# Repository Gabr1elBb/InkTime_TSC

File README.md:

## InkTime - Smartwatch Project
Open-source smartwatch hardware project based on the Nordic nRF52840 MCU, 
featuring a 1.54" e-paper display and optimized for ultra-low power consumption. 

## Block Diagram
```text
[ USB Type-C ]     [ LiPo Battery (250mAh) ]
           | 5V VBUS          |
           v                  | BAT
    +---------------+         v
    |    BQ25180    |<--+ [MAX17048]
    |  (Charger IC) |   | (Fuel Gauge)
    +---------------+   |     |
           | VSYS       +-----+ I2C
           v                  v
    +---------------+      +-------------+
    |    RT6160     |      |             |
    | (Buck-Boost)  |      |  nRF52840   |
    +---------------+      |     MCU     |
           | 3.3V (VDD_3V3)|  (Control   |
           | System Rail   |    Hub)     |
           |               |             |
 +---------+---------------+------+------+
 |         |               |      |
 |         v               |      |
 |  +-------------+        |      | SPI
 |  | PFET Switch |<--GPIO-+      v
 |  +------+------+        |  +-------------+
 |         | VEPD          |  | 1.54" E-paper|
 |         v               |  |   Display   |
 |  +-------------+        |  +-------------+
 |  | [Display]   |        |
 |  +-------------+        | I2C Bus
 |                         |
 +---I2C==> [ BMA421 Accel ]
 |                         |
 +---I2C==> [ DRV2605L Driver ] --> [ Vibration Motor ]
 |
 |          [ PCB Antenna ] <--> [ BLE RF ]
 |
 +---GPIO-> [ User Buttons ]
```

## Bill Of Materials (BOM)

| Designator | Component | Package | Manufacturer | Description / Notes |
| :--- | :--- | :--- | :--- | :--- |
| **U1** | [**nRF52840**](https://www.nordicsemi.com/Products/nRF52840) | aQFN-73 | Nordic Semi | SoC Bluetooth 5.0 (Procesor principal) |
| **IC1** | [**BQ25180Y**](https://www.ti.com/product/BQ25180) | DSBGA-8 | Texas Inst. | Charger IC Li-Ion (Management baterie) |
| **IC2** | [**DRV2605Y**](https://www.ti.com/product/DRV2605) | DSBGA-9 | Texas Inst. | Haptic Driver (Control motor vibrații) |
| **IC9** | [**RT6160AWSC**](https://www.richtek.com/Products/Product%20List/RT6160) | WLCSP-15 | RICHTEK | Buck-Boost Regulator 3.3V |
| **IC3** | [**BMA423**](https://www.bosch-sensortec.com/products/motion-sensors/accelerometers/bma423/) | LGA-12 | BOSCH | Accelerometru (Detectie miscare) |
| **U3 / IC6** | [**MAX17048**](https://www.analog.com/en/products/max17048.html) | TDFN-8 | Maxim/ADI | Monitorizare nivel baterie (Fuel Gauge) |
| **ANT1** | [**2450AT18B100E**](https://www.johansontechnology.com/datasheets/2450AT18B100E.pdf) | 1.4mm | JOHANSON | Antena Chip 2.45GHz |
| **J1** | [**503480-2400**](https://www.molex.com/en-us/products/part-detail/5034802400) | FPC-24 | Molex | Conector ecran (0.5mm pitch) |
| **J4** | [**KH-TYPE-C-16P**](https://www.kinghelm.com.cn/product-item-1589.html) | SMT | Kinghelm | Port USB Type-C |
| **Q3** | [**SI1308EDL**](https://www.vishay.com/en/product/71996/) | SOT-323 | Vishay | MOSFET N-Ch (Comutare putere) |
| **D3** | [**USBLC6-2**](https://www.st.com/en/protection-devices/usblc6-2sc6y.html) | SOT-23-6 | STMicro | Protectie ESD linii date USB |
| **X1, X2** | **Crystal** | 2016 / 2012 | Generic | Cuart 32MHz (Sistem) / 32.768kHz (RTC) |
| **L2** | **10µH** | 0402 | Generic | Inductor critic pentru circuitul de boost e-Paper |
| **R1_EP_DR** | **0.47 Ω** | 0201 | Generic | Rezistenta de sens (RESE) pentru ecran |
| **R5, R7, R8** | **10k Ω** | 0201 | Generic | Rezistente Pull-up (I2C / Linii control) |
| **C1-EP-DR, C39** | **10µF** | 0201 | Generic | Condensatori filtrare alimentare |
| **C1, C2, C17, C18** | **12pF** | 0201 | Generic | Condensatori pentru cuart (X1, X2) |
| **C2-EP-DR** | **4.7µF / 25V** | 0201 | Generic | Stocare energie tensiuni mari ecran (VGH/VGL) |
## Hardware Implementation Details

### Energy Management Strategy
To ensure maximum runtime, the system implements a **dual-stage power topology**. The **BQ25180** manages the LiPo charging cycle and provides a system voltage (**VSYS**), which is then regulated to a stable **3.3V** by the **RT6160 Buck-Boost**. The use of a Buck-Boost instead of a standard LDO allows the system to remain operational even as the battery voltage drops significantly below 3.3V.

### Display Power Gating
The E-paper display is inherently energy-efficient as it only draws power during image refreshes. However, to eliminate leakage current during sleep cycles, a **PFET high-side switch (SI2301)** is used. The MCU physically disconnects the display's power rail (**VEPD**) between updates via a dedicated GPIO signal.

### Haptic Feedback and Sensing
Unlike simple vibration circuits, the **DRV2605L** driver provides sophisticated haptic patterns. It controls an **ERM motor** via I2C commands. Motion tracking is handled by the **BMA421**, which monitors steps and orientation in the background, waking the nRF52840 only when necessary via hardware interrupts.

---

## Pinout Mapping (nRF52840)

### Shared I2C Bus
Used by the IMU (BMA421), Fuel Gauge (MAX17048), Li-Po Charger (BQ25180), Haptic Driver (DRV2605), and DC/DC Converter (RT6160).
* **P0.16** — SDA (Serial Data)
* **P0.14** — SCL (Serial Clock)

### E-Paper Display (SPI Interface)
Connected via the 24-pin FPC connector (J1).
* **P0.17** — EPD_SCK (Serial Clock)
* **P0.22** — EPD_MOSI (Serial Data)
* **P0.20** — EPD_CS (Chip Select)
* **P0.13** — EPD_DC (Data/Command Selection)
* **P0.24** — EPD_RST (Hardware Reset)
* **P0.11** — EPD_BUSY (Panel Status Input)

### Peripheral Interrupts & Control
* **P0.15** — CHG_INT (Charger state/interrupt)
* **P0.25** — IMU_INT1 (Primary motion interrupt)
* **P0.26** — IMU_INT2 (Secondary motion interrupt)
* **P0.06** — HAPTIC_INT (Haptic driver control/interrupt)
* **P0.08** — FUEL_ALERT (Battery fuel gauge alert)

### Physical Buttons (Internal Pull-up, Active-Low)
* **P1.11** — BTN_UP (Up Navigation)
* **P1.13** — BTN_ENT (Enter / Select)
* **P1.15** — BTN_DN (Down Navigation)

### Debug & System Clocks
* **XC1/XC2 & XL1/XL2** — External 32MHz and 32.768kHz crystals for system and RTC stability.
* **SWDIO, SWDCLK, SWO, nRESET** — Routed to the Tag-Connect TC2030 debug interface for firmware flashing and real-time debugging.

# Design Log

## Schematic Design

- **nRF52840** (aQFN-73) selected as main MCU, providing Bluetooth 5.0, native USB and sufficient GPIOs for all peripherals.
- **Dual-stage power topology**: BQ25180YBGR handles LiPo charging, RT6160AWSC Buck-Boost regulates the 3.3V system rail — allowing operation even as battery drops below 3.3V.
- **MAX17048** fuel gauge connected on shared I2C for accurate battery level estimation.
- **BMA421** triaxial accelerometer on I2C with two hardware interrupt lines to the MCU.
- **2450AT18B100E** chip antenna with discrete matching network for 2.4GHz BLE.
- Dedicated e-paper drive circuit (MBR0530, SI1308EDL, boost inductor) generating PREVGH/PREVGL voltages for the 1.54" panel via a 24-pin Molex FPC connector.
- **DRV2605YZFR** haptic driver for ERM motor, controlled via I2C.
- **USBLC6-2SC6Y** ESD protection on USB lines, KH-TYPE-C-16P connector with 5.1kΩ CC resistors for power delivery negotiation.
- Three tactile buttons (UP, DOWN, ENTER) with 10kΩ pull-ups.
- **TC2030-IDC** SWD connector with dedicated test points for programming and debug.

---

## PCB Design
- Smartwatch form factor sized for wrist-wear with a dedicated enclosure.
- Antenna and matching network placed at PCB edge with no copper pour underneath, per Nordic's nRF52840 layout guidelines.
- 100nF decoupling capacitors placed close to each nRF52840 power pin (DEC1–DEC6).
- Manufacturing files (Gerber, BOM, CPL) available in `/Manufacturing`.

---

## 3D Design

- Enclosure designed to house the PCB, 250mAh LiPo and 1.54" e-paper display.
- 3D assembly model available in `/Images` for fit and clearance verification.
- USB Type-C and side buttons (UP, DOWN, ENTER) accessible without disassembly.

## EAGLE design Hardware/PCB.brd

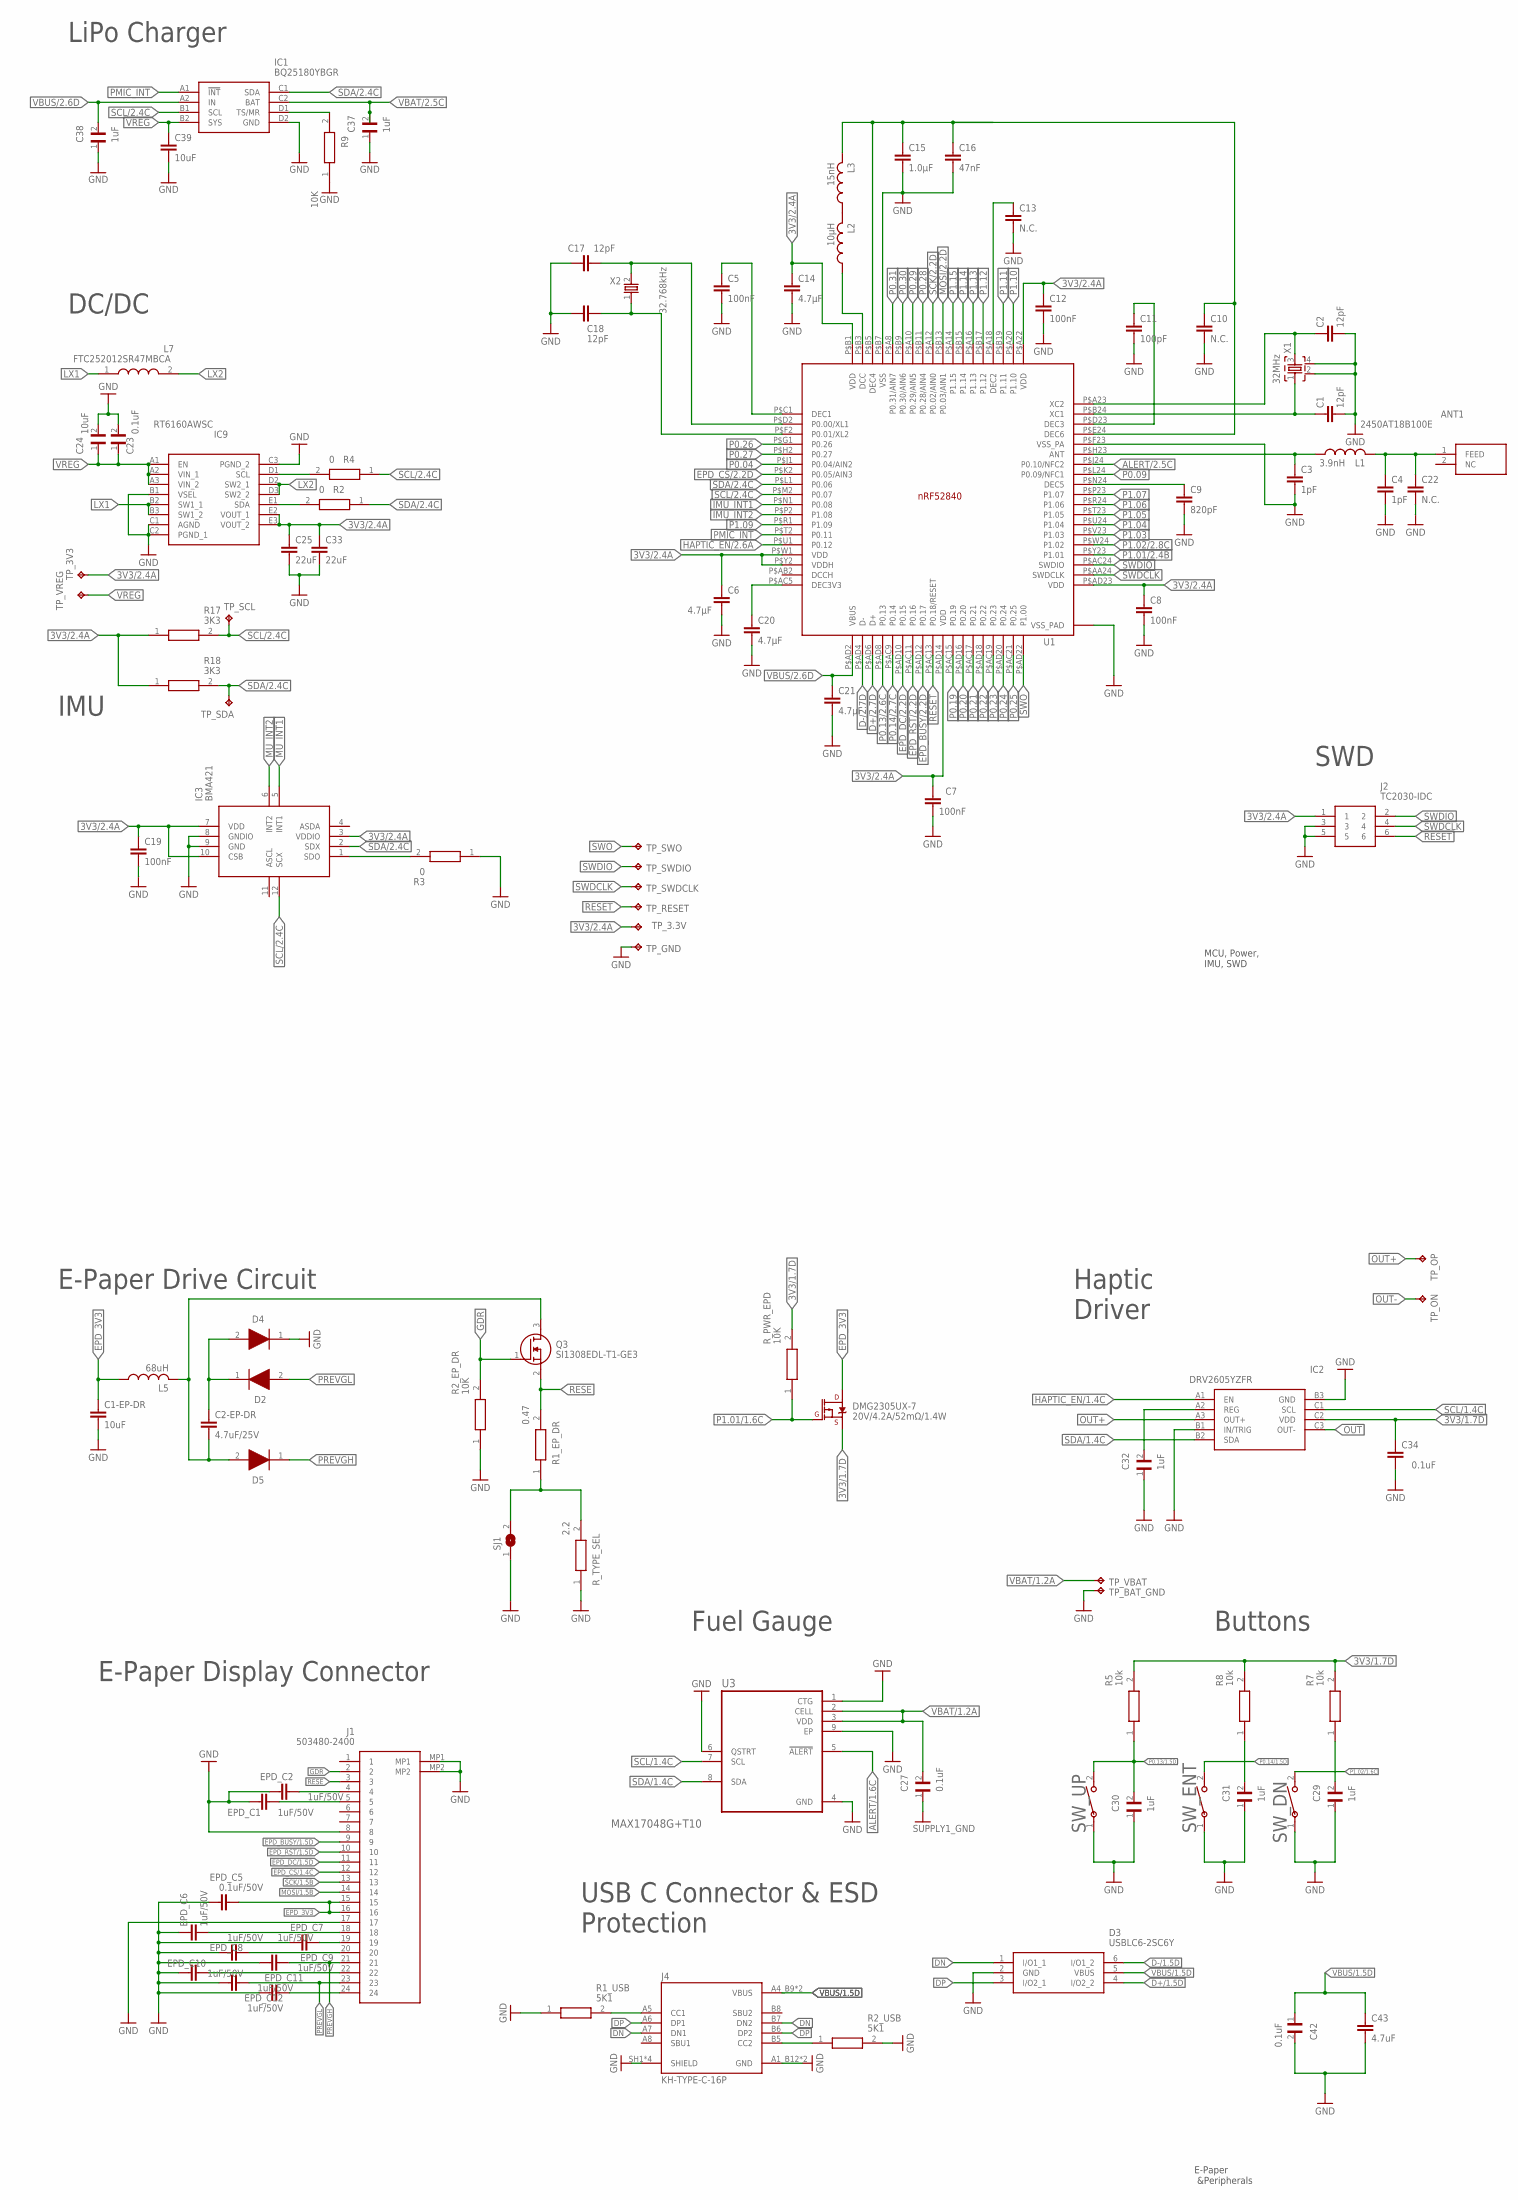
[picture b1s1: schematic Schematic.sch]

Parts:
ANT1: 2450AT18B100E; 2450AT18B100E_ANTC3216X140N
C1, C2, C17, C18: 12pF; NORDIC_NRF_3_RESC0201_L
C1-EP-DR, C39: 10uF; NORDIC_NRF_3_RESC0201_L
C2-EP-DR: 4.7uF/25V; NORDIC_NRF_3_RESC0201_L
C3, C4: 1pF; NORDIC_NRF_3_RESC0201_L
C5, C7, C8, C12, C19: 100nF; NORDIC_NRF_3_RESC0201_L
C6: 4.7µF; NORDIC_NRF_3_RESC0201_L
C9: 820pF; NORDIC_NRF_3_RESC0201_L
C10, C13, C22: N.C.; NORDIC_NRF_3_RESC0201_L
C11: 100pF; NORDIC_NRF_3_RESC0201_L
C14, C20, C21: 4.7µF; PERFECT_0402_0402
C15: 1.0µF; NORDIC_NRF_3_RESC0201_L
C16: 47nF; NORDIC_NRF_3_RESC0201_L
C23, C27, C42: 0.1uF; GRM011R60J152KE01L_2_CAPC0201X13N
C24: 10uF; GRM011R60J152KE01L_2_CAPC0201X13N
C25, C33: 22uF; PERFECT_0402_0402
C29, C30, C31, C32, C37, C38: 1uF; GRM011R60J152KE01L_2_CAPC0201X13N
C34: 0.1uF; NORDIC_NRF_3_RESC0201_L
C43: 4.7uF; PERFECT_0402_0402
D2, D4, D5: ESP32_C6_LIBRARY_5_MBR0530; ESP32_C6_LIBRARY_5_SOD3716X135N
D3: USBLC6-2SC6Y; ESP32_C6_LIBRARY_3_SOT95P280X145-6N
DMG2305UX-7: 20V/4.2A/52mΩ/1.4W; ESP32_C6_LIBRARY_4_ESP32_C6_LIBRARY_4_ESP32_C6_LIBRARY_4_ES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
EPD_C1, EPD_C2, EPD_C6, EPD_C7, EPD_C8, EPD_C9, EPD_C10, EPD_C11, EPD_C12: 1uF/50V; PERFECT_0402_0402
EPD_C5: 0.1uF/50V; PERFECT_0402_0402
IC1: BQ25180YBGR; BQ25180YBGR_BGA8C40P2X4_100X155X50
IC2: DRV2605YZFR; DRV2605YZFR_BGA9C50P3X3_144X144X62
IC3: BMA421; BMA423_BMA423
IC9: RT6160AWSC; RT6160AWSC_BGA15C40P3X5_140X230X60
J1: 503480-2400; 503480-2400_5034802400
J2: TC2030-IDC; TC2030-IDC_TC2030IDC
J4: KH-TYPE-C-16P; KH-TYPE-C-16P_KINGHELM_KH-TYPE-C-16P
L1: 3.9nH; NORDIC_NRF_2_RESC0402_L
L2: 10µH; NORDIC_NRF_2_RESC0402_L
L3: 15nH; NORDIC_NRF_2_RESC0402_L
L5: 68uH; NORDIC_NRF_2_RESC0402_L
L7: FTC252012SR47MBCA; MLP2016SR47MT0S1_INDC2016X100N
Q3: SI1308EDL-T1-GE3; ESP32_C6_LIBRARY_6_SOT65P210X110-3N
R1_EP_DR: 0.47; ERA-1AEB3401C_0201
R1_USB: 5K1; CPF0201D7K68C1_0201
R2, R4: 0; CPF0201D7K68C1_0201
R2_EP_DR, R9: 10K; ERA-1AEB3401C_0201
R2_USB: 5K1; ERA-1AEB3401C_0201
R3: 0; ERA-1AEB3401C_0201
R5, R7, R8: 10k; CPF0201D7K68C1_0201
R17, R18: 3K3; CPF0201D7K68C1_0201
R_PWR_EPD: 10K; CPF0201D7K68C1_0201
R_TYPE_SEL: 2.2; ERA-1AEB3401C_0201
SJ1: ESP32_C6_LIBRARY_7_JUMPER_SJ
SW_DN: 2025-10-22_07-23-44_LIBRARY_EVP-AKE31ASW_EVP-AKE3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; 2025-10-22_07-23-44_LIBRARY_SW_EVP-AKE31A_PAN
SW_ENT: 2025-10-22_07-23-44_LIBRARY_EVP-AKE31ASW_EVP-AKE3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; 2025-10-22_07-23-44_LIBRARY_SW_EVP-AKE31A_PAN
SW_UP: 2025-10-22_07-23-44_LIBRARY_EVP-AKE31ASW_EVP-AKE3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; 2025-10-22_07-23-44_LIBRARY_SW_EVP-AKE31A_PAN
TP_3.3V, TP_3V3: HECTOR_WATCH_1_TPTP20R; HECTOR_WATCH_1_TP20R
TP_BAT_GND: HECTOR_WATCH_1_TPTP20R; HECTOR_WATCH_1_TP20R
TP_GND: HECTOR_WATCH_1_TPTP20R; HECTOR_WATCH_1_TP20R
TP_ON: HECTOR_WATCH_1_TPTP20R; HECTOR_WATCH_1_TP20R
TP_OP: HECTOR_WATCH_1_TPTP20R; HECTOR_WATCH_1_TP20R
TP_RESET: HECTOR_WATCH_1_TPTP20R; HECTOR_WATCH_1_TP20R
TP_SCL: HECTOR_WATCH_1_TPTP20R; HECTOR_WATCH_1_TP20R
TP_SDA: HECTOR_WATCH_1_TPTP20R; HECTOR_WATCH_1_TP20R
TP_SWDCLK: HECTOR_WATCH_1_TPTP20R; HECTOR_WATCH_1_TP20R
TP_SWDIO: HECTOR_WATCH_1_TPTP20R; HECTOR_WATCH_1_TP20R
TP_SWO: HECTOR_WATCH_1_TPTP20R; HECTOR_WATCH_1_TP20R
TP_VBAT: HECTOR_WATCH_1_TPTP20R; HECTOR_WATCH_1_TP20R
TP_VREG: HECTOR_WATCH_1_TPTP20R; HECTOR_WATCH_1_TP20R
U1: NRF52840_QF; NORDIC_NRF_4_AQFN50P700X700X85_HS-74N
U3: MAX17048G+T10; ESP32_C6_LIBRARY_SON50P200X200X80-9N
X1: 32MHz; NORDIC_NRF_BT-XTAL_2016_N
X2: 32.768kHz; NORDIC_NRF_1_XTAL_3215_N

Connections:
3V3/1.7D: C34.1, DMG2305UX-7.2 (S), IC2.C2 (VDD), R5.2, R7.2, R8.2, R_PWR_EPD.2
3V3/2.4A: C6.1, C7.1, C8.1, C12.1, C14.1, C19.1, C25.1, C33.1, IC3.3 (VDDIO), IC3.7 (VDD), IC3.10 (CSB), IC9.E2 (VOUT_1), IC9.E3 (VOUT_2), J2.1, R17.1, R18.1, TP_3.3V.TP, TP_3V3.TP, U1.P$A22 (VDD), U1.P$AD14 (VDD), U1.P$AD23 (VDD), U1.P$B1 (VDD), U1.P$W1 (VDD), U1.P$Y2 (VDDH)
ALERT/1.6C: U3.5 (!ALERT)
ALERT/2.5C: U1.P$J24 (P0.10/NFC2)
D+/1.5D: D3.4 (I/O2_2)
D+/2.7D: U1.P$AD6 (D+)
D-/1.5D: D3.6 (I/O1_2)
D-/2.7D: U1.P$AD4 (D-)
DN: D3.1 (I/O1_1), J4.A7 (DN1), J4.B7 (DN2)
DP: D3.3 (I/O2_1), J4.A6 (DP1), J4.B6 (DP2)
EPD_3V3: C1-EP-DR.1, DMG2305UX-7.3 (D), EPD_C5.2, J1.15, J1.16, L5.1
EPD_BUSY/1.5D: J1.9
EPD_BUSY/2.2D: U1.P$AD12 (P0.17)
EPD_CS/1.4C: J1.12
EPD_CS/2.2D: U1.P$K2 (P0.05/AIN3)
EPD_DC/1.5D: J1.11
EPD_DC/2.2D: U1.P$AD10 (P0.15)
EPD_RST/1.5D: J1.10
EPD_RST/2.2D: U1.P$AC11 (P0.16)
GDR: J1.2, Q3.1 (G), R2_EP_DR.2
GND: C1.2, C1-EP-DR.2, C2.2, C3.2, C4.2, C5.2, C6.2, C7.2, C8.2, C9.2, C10.2, C11.2, C12.2, C13.2, C14.2, C15.2, C16.2, C17.1, C18.2, C19.2, C20.2, C21.2, C22.2, C23.2, C24.2, C25.2, C27.1, C29.1, C30.1, C31.1, C32.1, C33.2, C34.2, C37.1, C38.1, C39.2, C42.2, C43.2, D3.2 (GND), D4.1 (K), EPD_C1.1, EPD_C2.1, EPD_C5.1, EPD_C6.1, EPD_C7.1, EPD_C8.1, EPD_C9.1, EPD_C10.1, EPD_C11.1, EPD_C12.1, IC1.D2 (GND), IC2.B1 (IN/TRIG), IC2.B3 (GND), IC3.8 (GNDIO), IC3.9 (GND), IC9.B1 (VSEL), IC9.C1 (AGND), IC9.C2 (PGND_1), IC9.C3 (PGND_2), J1.8, J1.17, J1.MP1, J1.MP2, J2.3, J2.5, J4.A1_B12 (GND), J4.A12_B1 (GND), J4.SH1 (SHIELD), J4.SH2 (SHIELD), J4.SH3 (SHIELD), J4.SH4 (SHIELD), R1_USB.1, R2_EP_DR.1, R2_USB.2, R3.1, R9.1, R_TYPE_SEL.1, SJ1.1, SW_DN.1, SW_ENT.1, SW_UP.1, TP_BAT_GND.TP, TP_GND.TP, U1.P$74 (VSS_PAD), U1.P$75 (VSS_PAD), U1.P$76 (VSS_PAD), U1.P$77 (VSS_PAD), U1.P$78 (VSS_PAD), U1.P$79 (VSS_PAD), U1.P$80 (VSS_PAD), U1.P$81 (VSS_PAD), U1.P$82 (VSS_PAD), U1.P$83 (VSS_PAD), U1.P$84 (VSS_PAD), U1.P$85 (VSS_PAD), U1.P$86 (VSS_PAD), U1.P$87 (VSS_PAD), U1.P$88 (VSS_PAD), U1.P$89 (VSS_PAD), U1.P$90 (VSS_PAD), U1.P$B7 (VSS), U1.P$F23 (VSS_PA), U3.1 (CTG), U3.4 (GND), U3.6 (QSTRT), U3.9 (EP), X1.2, X1.4
HAPTIC_EN/1.4C: IC2.A1 (EN)
HAPTIC_EN/2.6A: U1.P$U1 (P0.12)
IMU_INT1: U1.P$N1 (P0.08)
IMU_INT2: U1.P$P2 (P1.08)
JJ: C10.1, C15.1, C16.1, L3.2, U1.P$B5 (DEC4), U1.P$E24 (DEC6)
LX1: IC9.B2 (SW1_1), IC9.B3 (SW1_2), L7.1
LX2: IC9.D2 (SW2_1), IC9.D3 (SW2_2), L7.2
MOSI/1.5B: J1.14
MOSI/2.2D: U1.P$B13 (P0.03/AIN1)
MU_INT1: IC3.5 (INT1)
MU_INT2: IC3.6 (INT2)
unnamed: IC1.D1 (TS/MR), R9.2
unnamed: IC9.D1 (SCL), R4.2
unnamed: IC9.E1 (SDA), R2.2
unnamed: IC3.1 (SDO), R3.2
unnamed: C20.1, U1.P$AC5 (DEC3V3)
unnamed: C18.1, U1.P$F2 (P0.01/XL2), X2.1
unnamed: C17.2, U1.P$D2 (P0.00/XL1), X2.2
unnamed: C5.1, U1.P$C1 (DEC1)
unnamed: C9.1, U1.P$N24 (DEC5)
unnamed: L2.1, U1.P$B3 (DCC)
unnamed: L2.2, L3.1
unnamed: C3.1, L1.1, U1.P$H23 (ANT)
unnamed: ANT1.1 (FEED), C4.1, C22.1, L1.2
unnamed: C11.1, U1.P$D23 (DEC3)
unnamed: C2.1, U1.P$A23 (XC2), X1.3
unnamed: C1.1, U1.P$B24 (XC1), X1.1
unnamed: C2-EP-DR.2, D5.2 (A), L5.2, Q3.3 (D)
unnamed: C2-EP-DR.1, D2.1 (K), D4.2 (A)
unnamed: R1_EP_DR.1, R_TYPE_SEL.2, SJ1.2
unnamed: C13.1, U1.P$A18 (DEC2)
unnamed: C32.2, IC2.A2 (REG)
unnamed: EPD_C2.2, J1.4
unnamed: EPD_C1.2, J1.5
unnamed: EPD_C6.2, J1.18
unnamed: EPD_C7.2, J1.19
unnamed: EPD_C8.2, J1.20
unnamed: J4.A5 (CC1), R1_USB.2
unnamed: EPD_C10.2, J1.22
unnamed: C31.2, R8.1
unnamed: EPD_C12.2, J1.24
unnamed: J4.B5 (CC2), R2_USB.1
unnamed: C29.2, R7.1
OUT: IC2.C3 (OUT-)
OUT+: IC2.A3 (OUT+), TP_OP.TP
OUT-: TP_ON.TP
P0.04: U1.P$J1 (P0.04/AIN2)
P0.09: U1.P$L24 (P0.09/NFC1)
P0.13/1.5D: C30.2, R5.1, SW_UP.2
P0.13/2.6C: U1.P$AD8 (P0.13)
P0.14/1.5D: SW_ENT.2
P0.14/2.7C: U1.P$AC9 (P0.14)
P0.19: U1.P$AC15 (P0.19)
P0.20: U1.P$AD16 (P0.20)
P0.21: U1.P$AC17 (P0.21)
P0.22: U1.P$AD18 (P0.22)
P0.23: U1.P$AC19 (P0.23)
P0.24: U1.P$AD20 (P0.24)
P0.25: U1.P$AC21 (P0.25)
P0.26: U1.P$G1 (P0.26)
P0.27: U1.P$H2 (P0.27)
P0.28: U1.P$B11 (P0.28/AIN4)
P0.29: U1.P$A10 (P0.29/AIN5)
P0.30: U1.P$B9 (P0.30/AIN6)
P0.31: U1.P$A8 (P0.31/AIN7)
P1.01/1.6C: DMG2305UX-7.1 (G), R_PWR_EPD.1
P1.01/2.4B: U1.P$Y23 (P1.01)
P1.02/1.6C: SW_DN.2
P1.02/2.8C: U1.P$W24 (P1.02)
P1.03: U1.P$V23 (P1.03)
P1.04: U1.P$U24 (P1.04)
P1.05: U1.P$T23 (P1.05)
P1.06: U1.P$R24 (P1.06)
P1.07: U1.P$P23 (P1.07)
P1.09: U1.P$R1 (P1.09)
P1.10: U1.P$A20 (P1.10)
P1.11: U1.P$B19 (P1.11)
P1.12: U1.P$B17 (P1.12)
P1.13: U1.P$A16 (P1.13)
P1.14: U1.P$B15 (P1.14)
P1.15: U1.P$A14 (P1.15)
PMIC_INT: IC1.A1 (!INT), U1.P$T2 (P0.11)
PREVGH: D5.1 (K), EPD_C9.2, J1.21
PREVGL: D2.2 (A), EPD_C11.2, J1.23
RESE: J1.3, Q3.2 (S), R1_EP_DR.2
RESET: J2.6, TP_RESET.TP, U1.P$AC13 (P0.18/RESET)
SCK/1.5B: J1.13
SCK/2.2D: U1.P$A12 (P0.02/AIN0)
SCL/1.4C: IC2.C1 (SCL), U3.7 (SCL)
SCL/2.4C: IC1.B1 (SCL), IC3.12 (SCX), R4.1, R17.2, TP_SCL.TP, U1.P$M2 (P0.07)
SDA/1.4C: IC2.B2 (SDA), U3.8 (SDA)
SDA/2.4C: IC1.C1 (SDA), IC3.2 (SDX), R2.1, R18.2, TP_SDA.TP, U1.P$L1 (P0.06)
SWDCLK: J2.4, TP_SWDCLK.TP, U1.P$AA24 (SWDCLK)
SWDIO: J2.2, TP_SWDIO.TP, U1.P$AC24 (SWDIO)
SWO: TP_SWO.TP, U1.P$AD22 (P1.00)
VBAT/1.2A: C27.2, TP_VBAT.TP, U3.2 (CELL), U3.3 (VDD)
VBAT/2.5C: C37.2, IC1.C2 (BAT)
VBUS/1.5D: C42.1, C43.1, D3.5 (VBUS), J4.A4_B9 (VBUS), J4.A9_B4 (VBUS)
VBUS/2.6D: C21.1, C38.2, IC1.A2 (IN), U1.P$AD2 (VBUS)
VREG: C23.1, C24.1, C39.1, IC1.B2 (SYS), IC9.A1 (EN), IC9.A2 (VIN_1), IC9.A3 (VIN_2), TP_VREG.TP

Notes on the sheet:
LiPo Charger
DC/DC
IMU
SWD
MCU, Power, IMU, SWD
E-Paper Drive Circuit
Haptic Driver
E-Paper Display Connector
Fuel Gauge
Buttons
E-Paper &Peripherals
USB C Connector & ESD Protection

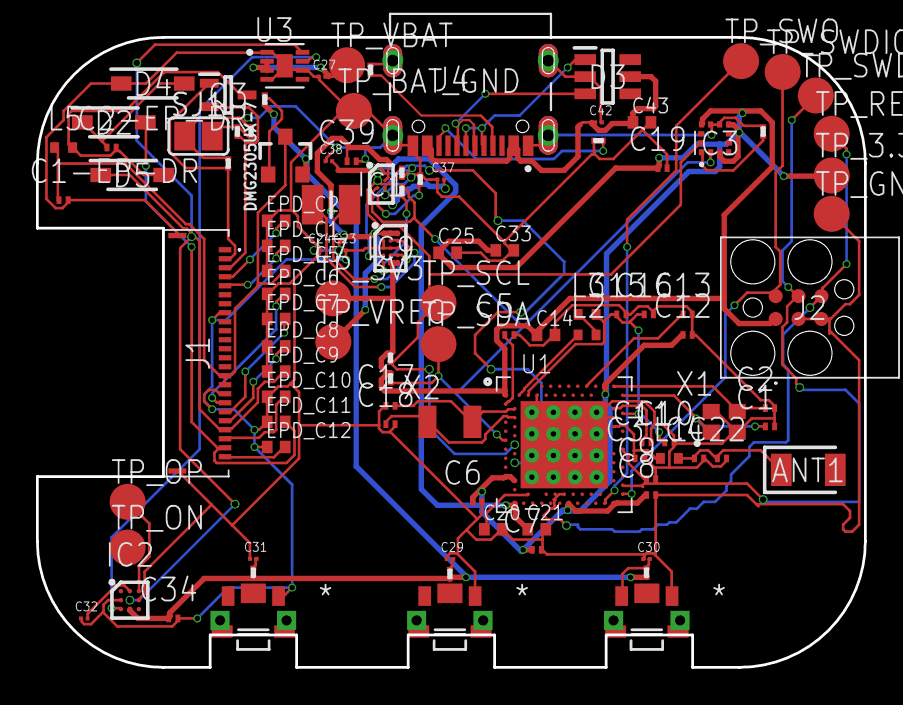
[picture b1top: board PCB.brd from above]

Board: 4 copper layers, 46.0 x 35.0 mm, 105 parts (0 on the bottom side), 62 nets.

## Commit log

2026-04-10 fold_inc
2026-04-19 Rename BOM.csv to BOM.bom
2026-04-19 Rename PnP.csv to PnP.cpl

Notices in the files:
parts and their libraries:
COPYRIGHT: Copyright (C) 2025 Ultra Librarian. All rights reserved.
